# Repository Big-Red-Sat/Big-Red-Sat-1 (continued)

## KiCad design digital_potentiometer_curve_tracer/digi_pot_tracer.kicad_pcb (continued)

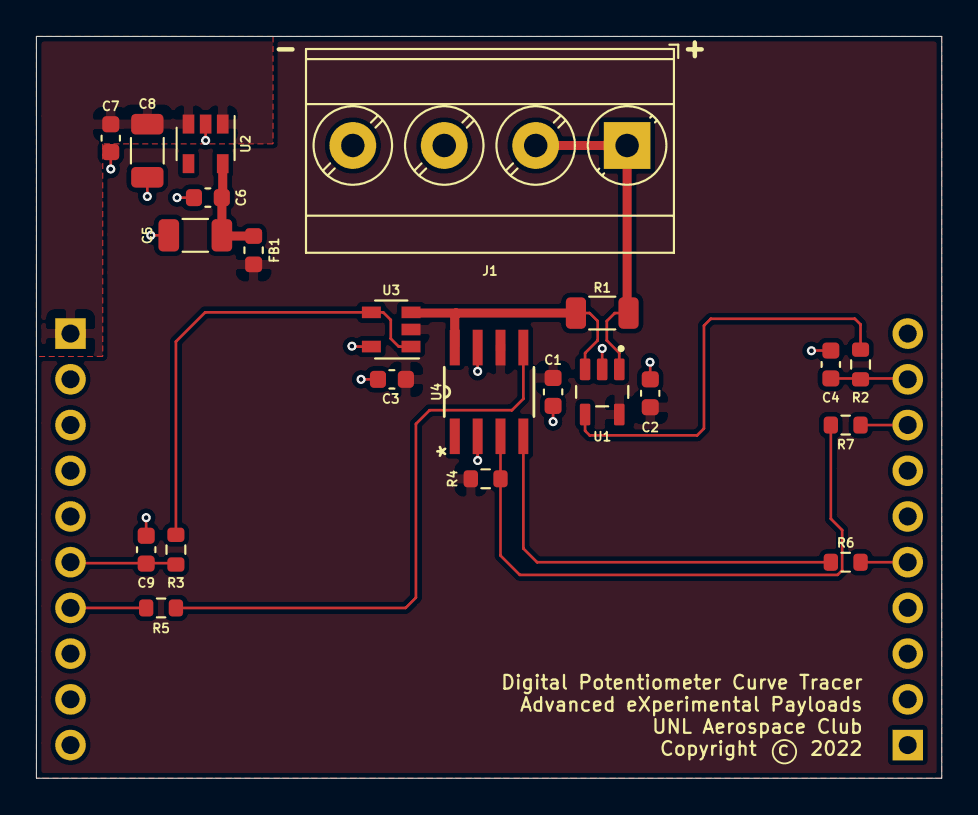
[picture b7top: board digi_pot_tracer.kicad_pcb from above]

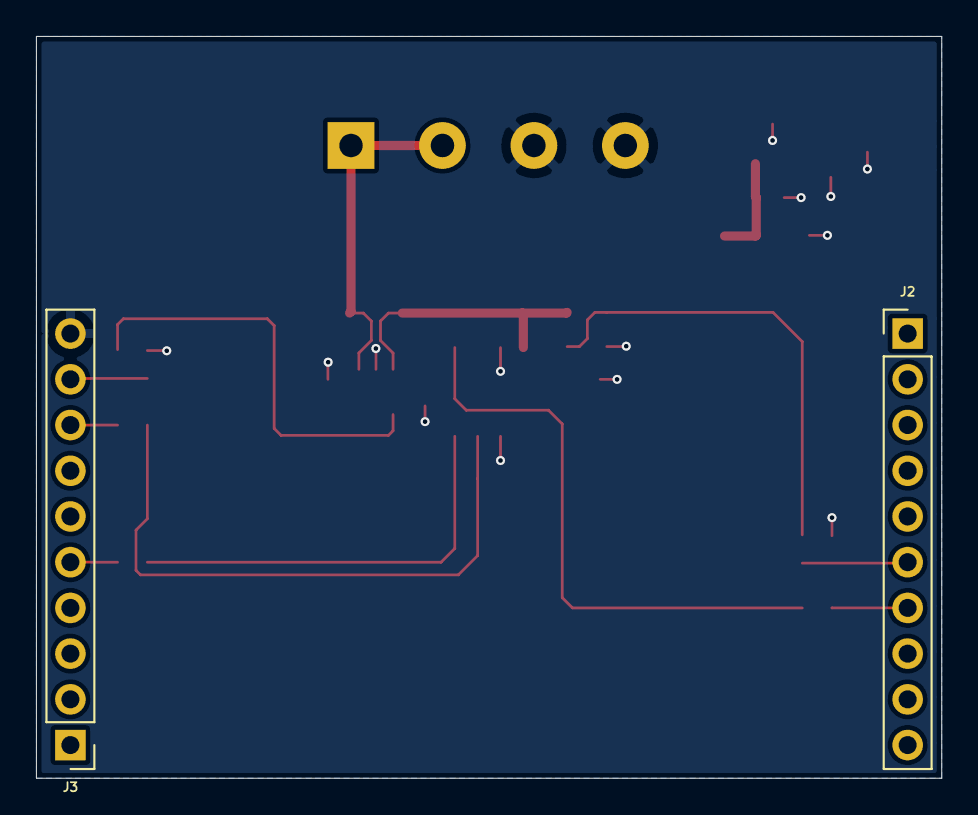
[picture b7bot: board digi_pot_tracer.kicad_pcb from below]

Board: 2 copper layers, 50.3 x 41.2 mm, 24 parts (2 on the bottom side), 16 nets.
